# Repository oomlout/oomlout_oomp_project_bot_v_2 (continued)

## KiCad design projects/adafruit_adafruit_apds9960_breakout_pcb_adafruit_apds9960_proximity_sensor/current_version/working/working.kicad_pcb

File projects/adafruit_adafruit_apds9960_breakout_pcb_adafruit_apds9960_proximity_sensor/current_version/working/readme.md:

# adafruit_apds9960_breakout_pcb
 
## summary 
* id: adafruit_adafruit_apds9960_breakout_pcb_adafruit_apds9960_proximity_sensor
* user: adafruit
* name: adafruit_apds9960_breakout_pcb
* board: adafruit_apds9960_proximity_sensor
* repo: https://github.com/adafruit/Adafruit-APDS9960-Breakout-PCB

* src_file_repo_sch: 
* src_file_repo_sch_link: https://github.com/adafruit/Adafruit-APDS9960-Breakout-PCB/tree/master/
* full details link: https://github.com/oomlout/oomlout_oomp_project_bot_v_2/tree/main/projects/adafruit_adafruit_apds9960_breakout_pcb_adafruit_apds9960_proximity_sensor/current_version/working  

## schematic  
  
[schematic (pdf)](working_schematic.pdf) 

## pcb  

[board (pdf)](working.pdf)  

## working_bom
| Id | Designator | Footprint | Quantity | Designation | Supplier and ref |  | None | 
| --- | --- | --- | --- | --- | --- | --- | --- | 
| 1 | U$17,U$21,U$1,U$19 | MOUNTINGHOLE_2.5_PLATED | 4 | MOUNTINGHOLE2.5 |  |  | [''] | 
| 2 | D1 | CHIPLED_0603_NOOUTLINE | 1 | GREEN |  |  | [''] | 
| 3 | Q2 | SOT363 | 1 | BSS138 |  |  | [''] | 
| 4 | CONN3,CONN4 | JST_SH4 | 2 | STEMMA_I2C_QT |  |  | [''] | 
| 5 | R1,R2 | 0603-NO | 2 | 10K |  |  | [''] | 
| 6 | U$22,U$2 | ADAFRUIT_3.5MM | 2 |  |  |  | [''] | 
| 7 | C3,C2 | 0805-NO | 2 | 10uF |  |  | [''] | 
| 8 | FID4,FID3 | FIDUCIAL_1MM | 2 | FIDUCIAL_1MM |  |  | [''] | 
| 9 | C1 | 0603-NO | 1 | 0.1uF |  |  | [''] | 
| 10 | U3 | APDS-9960 | 1 | APDS-9960 |  |  | [''] | 
| 11 | JP1 | 1X06_ROUND_70 | 1 |  |  |  | [''] | 
| 12 | U2 | SOT23-5 | 1 | AP2112K-3.3 |  |  | [''] | 
| 13 | R3 | RESPACK_4X0603 | 1 | 10K |  |  | [''] | 
| 14 | U$31,U$30 | STEMMAQT | 2 |  |  |  | [''] | 
| 15 | U$25 | PCBFEAT-REV-040 | 1 |  |  |  | [''] | 

## bom_schematic
| Ref | Qnty | Value | Cmp name | Footprint | Description | Vendor | DNP | 
| --- | --- | --- | --- | --- | --- | --- | --- | 
| C1 | 1 | 0.1uF | CAP_CERAMIC0603_NO | working:0603-NO |  |  |  | 
| C2, C3 | 2 | 10uF | CAP_CERAMIC0805-NOOUTLINE | working:0805-NO |  |  |  | 
| CONN3, CONN4 | 2 | STEMMA_I2C_QT | STEMMA_I2C_QT | working:JST_SH4 |  |  |  | 
| D1 | 1 | GREEN | LED0603_NOOUTLINE | working:CHIPLED_0603_NOOUTLINE |  |  |  | 
| FID3, FID4 | 2 | FIDUCIAL_1MM | FIDUCIAL_1MM | working:FIDUCIAL_1MM |  |  |  | 
| JP1 | 1 | HEADER-1X670MIL | HEADER-1X670MIL | working:1X06_ROUND_70 |  |  |  | 
| Q2 | 1 | BSS138 | MOSFET-N_DUAL | working:SOT363 |  |  |  | 
| R1, R2 | 2 | 10K | RESISTOR_0603_NOOUT | working:0603-NO |  |  |  | 
| R3 | 1 | 10K | RESISTOR_4PACK | working:RESPACK_4X0603 |  |  |  | 
| U2 | 1 | AP2112K-3.3 | VREG_SOT23-5 | working:SOT23-5 |  |  |  | 
| U3 | 1 | APDS-9960 | APDS-9960 | working:APDS-9960 |  |  |  | 
| U$1, U$17, U$19, U$21 | 4 | MOUNTINGHOLE2.5 | MOUNTINGHOLE2.5 | working:MOUNTINGHOLE_2.5_PLATED |  |  |  | 

## mounting_holes
| x | y | package | value | ref | size | 
| --- | --- | --- | --- | --- | --- | 
| 0.0 | 12.7 | MOUNTINGHOLE_2.5_PLATED | MOUNTINGHOLE2.5 | U$1 | m3 | 
| 20.32 | 12.7 | MOUNTINGHOLE_2.5_PLATED | MOUNTINGHOLE2.5 | U$17 | m3 | 
| 0.0 | 0.0 | MOUNTINGHOLE_2.5_PLATED | MOUNTINGHOLE2.5 | U$19 | m3 | 
| 20.32 | 0.0 | MOUNTINGHOLE_2.5_PLATED | MOUNTINGHOLE2.5 | U$21 | m3 |

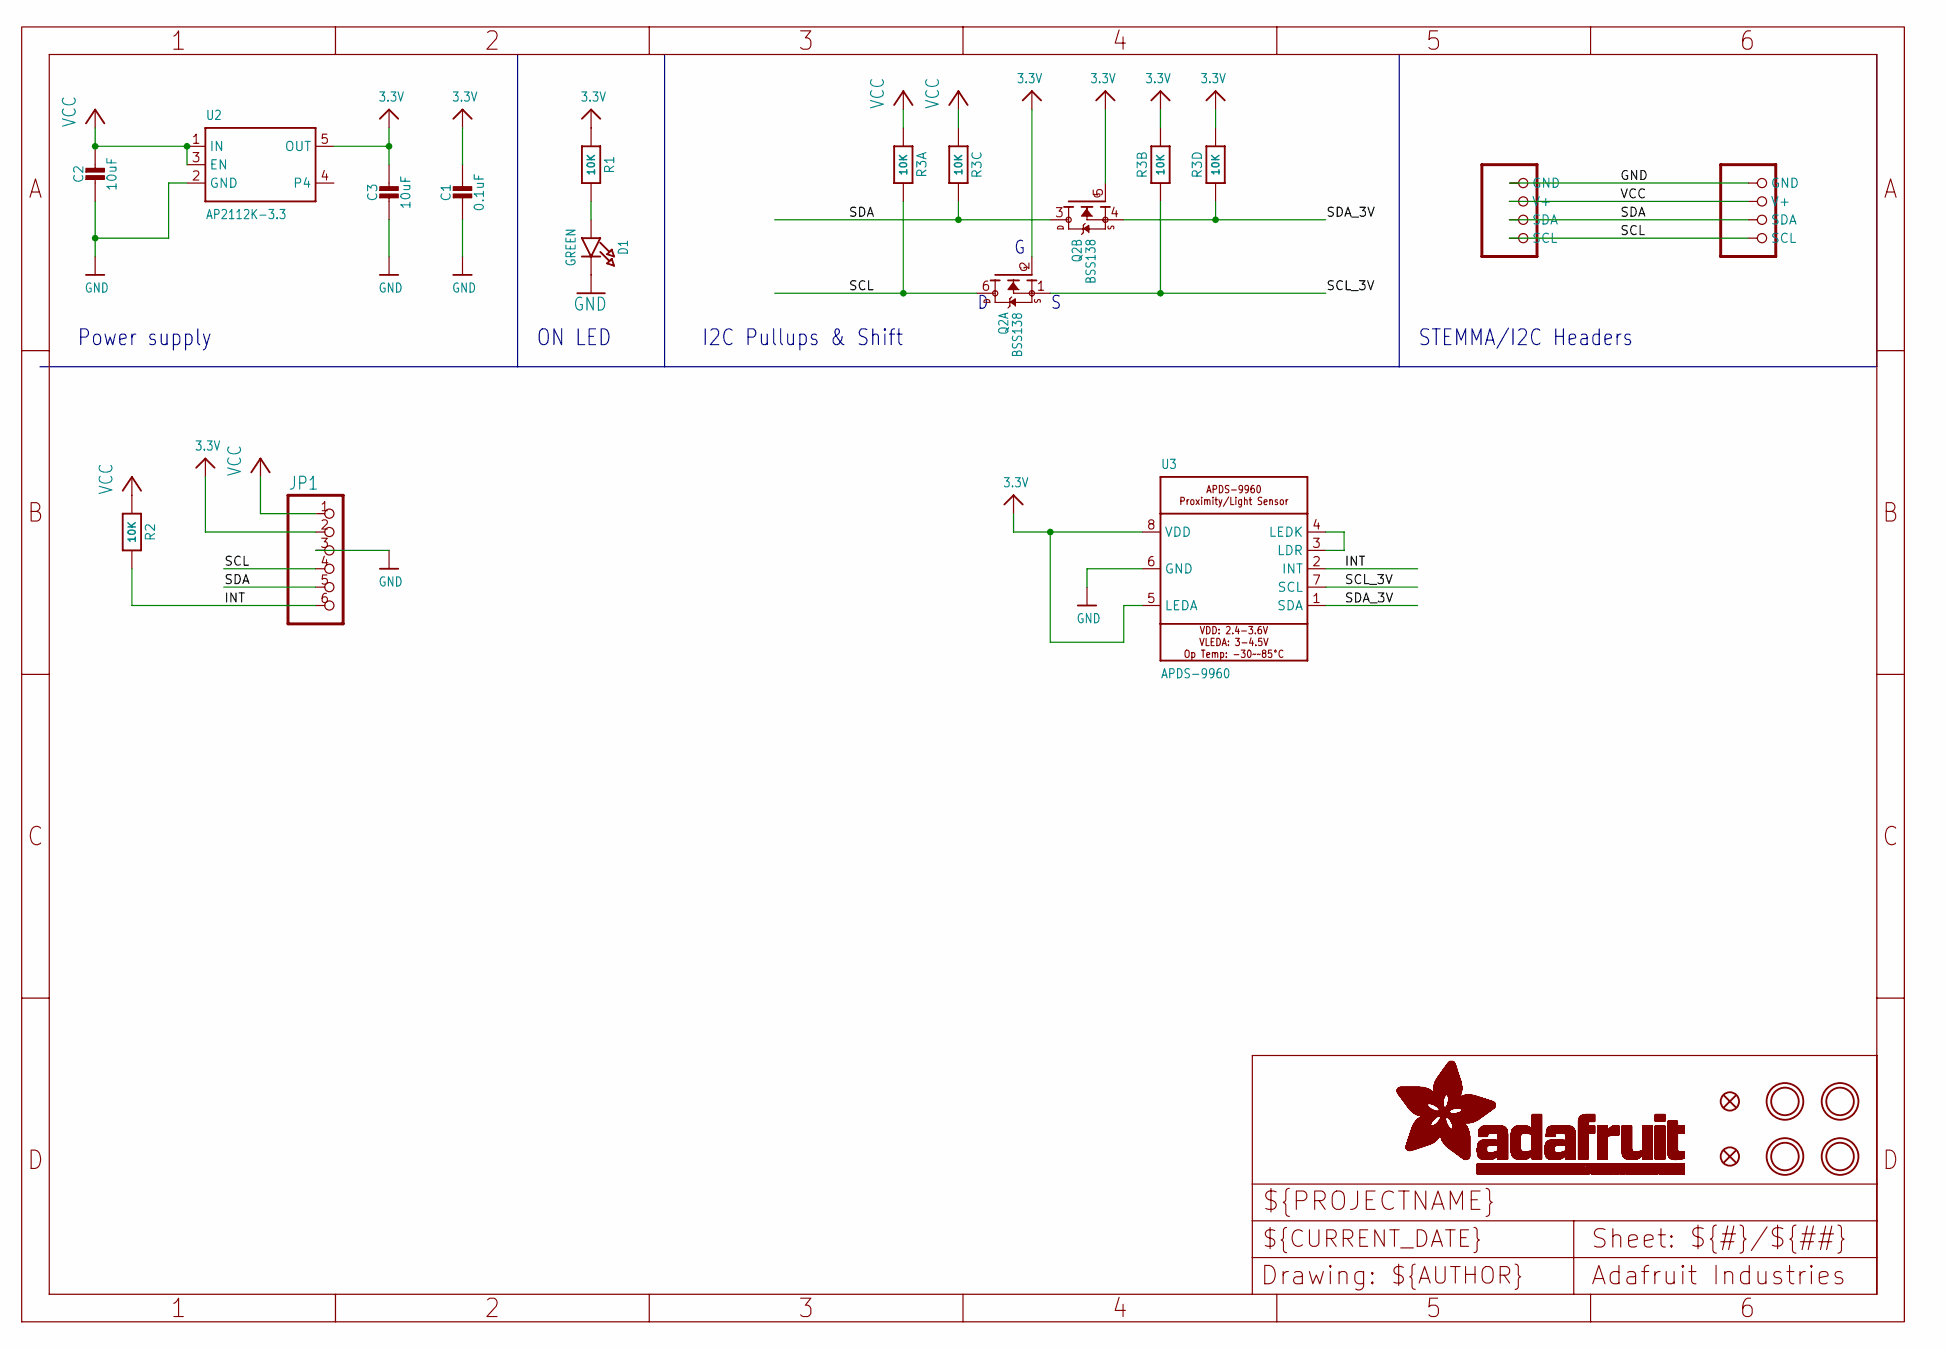
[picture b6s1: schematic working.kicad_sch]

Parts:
C1: 0.1uF; 0603-NO
C2, C3: 10uF; 0805-NO
CONN3, CONN4: STEMMA_I2C_QT; JST_SH4
D1: GREEN; CHIPLED_0603_NOOUTLINE
FID3, FID4: FIDUCIAL_1MM
JP1: HEADER-1X670MIL; 1X06_ROUND_70
Q2: BSS138; SOT363
R1, R2: 10K; 0603-NO
R3: 10K; RESPACK_4X0603
U2: AP2112K-3.3; SOT23-5
U3: APDS-9960
U$1, U$17, U$19, U$21: MOUNTINGHOLE2.5; MOUNTINGHOLE_2.5_PLATED

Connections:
3.3V: C1.1, C3.1, JP1.2, Q2.2 (G), Q2.5 (G), R1.1, R3.2 (1), R3.4 (1), U2.5 (OUT), U3.5 (LEDA), U3.8 (VDD)
GND: C1.2, C2.2, C3.2, CONN3.1 (GND), CONN4.1 (GND), D1.C, JP1.3, U2.2 (GND), U3.6 (GND)
INT: JP1.6, R2.2, U3.2 (INT)
unnamed: D1.A, R1.2
unnamed: U3.3 (LDR), U3.4 (LEDK)
SCL: CONN3.4 (SCL), CONN4.4 (SCL), JP1.4, Q2.6 (D), R3.8 (2)
SCL_3V: Q2.1 (S), R3.7 (2), U3.7 (SCL)
SDA: CONN3.3 (SDA), CONN4.3 (SDA), JP1.5, Q2.3 (D), R3.6 (2)
SDA_3V: Q2.4 (S), R3.5 (2), U3.1 (SDA)
VCC: C2.1, CONN3.2 (V+), CONN4.2 (V+), JP1.1, R2.1, R3.1, R3.3 (1), U2.1 (IN), U2.3 (EN)

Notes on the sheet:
ON LED
Power supply
I2C Pullups & Shift
STEMMA/I2C Headers

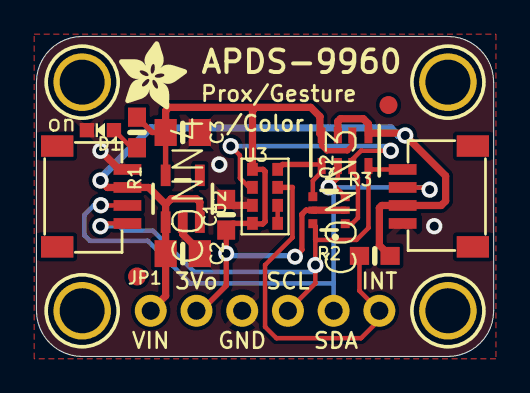
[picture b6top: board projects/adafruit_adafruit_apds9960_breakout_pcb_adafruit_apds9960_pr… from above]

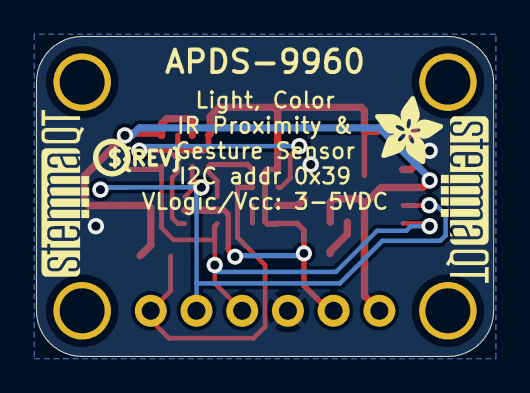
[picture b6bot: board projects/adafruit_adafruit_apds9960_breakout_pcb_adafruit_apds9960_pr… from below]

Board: 2 copper layers, 25.4 x 17.8 mm, 24 parts (4 on the bottom side), 10 nets.

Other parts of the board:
U$2, U$22: ADAFRUIT_3.5MM
U$25: PCBFEAT-REV-040
U$30, U$31: STEMMAQT

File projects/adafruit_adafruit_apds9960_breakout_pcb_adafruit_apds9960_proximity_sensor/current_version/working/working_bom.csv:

"Id";"Designator";"Footprint";"Quantity";"Designation";"Supplier and ref";
1;"U$17,U$21,U$1,U$19";"MOUNTINGHOLE_2.5_PLATED";4;"MOUNTINGHOLE2.5";;;
2;"D1";"CHIPLED_0603_NOOUTLINE";1;"GREEN";;;
3;"Q2";"SOT363";1;"BSS138";;;
4;"CONN3,CONN4";"JST_SH4";2;"STEMMA_I2C_QT";;;
5;"R1,R2";"0603-NO";2;"10K";;;
6;"U$22,U$2";"ADAFRUIT_3.5MM";2;"";;;
7;"C3,C2";"0805-NO";2;"10uF";;;
8;"FID4,FID3";"FIDUCIAL_1MM";2;"FIDUCIAL_1MM";;;
9;"C1";"0603-NO";1;"0.1uF";;;
10;"U3";"APDS-9960";1;"APDS-9960";;;
11;"JP1";"1X06_ROUND_70";1;"";;;
12;"U2";"SOT23-5";1;"AP2112K-3.3";;;
13;"R3";"RESPACK_4X0603";1;"10K";;;
14;"U$31,U$30";"STEMMAQT";2;"";;;
15;"U$25";"PCBFEAT-REV-040";1;"";;;

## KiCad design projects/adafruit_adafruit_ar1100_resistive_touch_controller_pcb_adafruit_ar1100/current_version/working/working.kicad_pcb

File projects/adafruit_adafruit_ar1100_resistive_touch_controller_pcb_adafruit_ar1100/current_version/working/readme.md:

# adafruit_ar1100_resistive_touch_controller_pcb
 
## summary 
* id: adafruit_adafruit_ar1100_resistive_touch_controller_pcb_adafruit_ar1100
* user: adafruit
* name: adafruit_ar1100_resistive_touch_controller_pcb
* board: adafruit_ar1100
* repo: https://github.com/adafruit/Adafruit-AR1100-Resistive-Touch-Controller-PCB

* src_file_repo_sch: 
* src_file_repo_sch_link: https://github.com/adafruit/Adafruit-AR1100-Resistive-Touch-Controller-PCB/tree/master/
* full details link: https://github.com/oomlout/oomlout_oomp_project_bot_v_2/tree/main/projects/adafruit_adafruit_ar1100_resistive_touch_controller_pcb_adafruit_ar1100/current_version/working  

## schematic  
  
[schematic (pdf)](working_schematic.pdf) 

## pcb  

[board (pdf)](working.pdf)  

## working_bom
| Id | Designator | Footprint | Quantity | Designation | Supplier and ref |  | None | 
| --- | --- | --- | --- | --- | --- | --- | --- | 
| 1 | FID1,FID3,FID2 | FIDUCIAL_1MM | 3 | FIDUCIAL" |  |  | [''] | 
| 2 | U$6,U$5,U$4,U$2 | MOUNTINGHOLE_2.5_PLATED | 4 | MOUNTINGHOLE2.5 |  |  | [''] | 
| 3 | D2,D3 | SOD-323F | 2 | 1N4148 |  |  | [''] | 
| 4 | IC1 | TSSOP20-5.3MMBODY | 1 | AR1100_SSOP |  |  | [''] | 
| 5 | C1 | 0805-NO | 1 | 0.1uF |  |  | [''] | 
| 6 | LED1 | CHIPLED_0805_NOOUTLINE | 1 | RED |  |  | [''] | 
| 7 | U$7 | FPC_CONN_1MM_DUAL_4P | 1 | FPC_4PIN_12969 |  |  | [''] | 
| 8 | X1 | USB-MINIB | 1 |  |  |  | [''] | 
| 9 | C2,C3 | 0805-NO | 2 | 10uF |  |  | [''] | 
| 10 | CN2,CN1 | 1X04-CLEANBIG | 2 | 1X4-CLEANBIG |  |  | [''] | 
| 11 | U$14 | ADAFRUIT_3.5MM | 1 |  |  |  | [''] | 
| 12 | R2 | 0805-NO | 1 | 20K |  |  | [''] | 
| 13 | R1 | 0805-NO | 1 | 470 |  |  | [''] | 
| 14 | Y1 | RESONATOR-SMD | 1 | 12MHz |  |  | [''] | 
| 15 | U$17 | ADAFRUIT_TEXT_20MM | 1 |  |  |  | [''] | 

## mounting_holes
| x | y | package | value | ref | size | 
| --- | --- | --- | --- | --- | --- | 
| 0.0 | 0.0 | MOUNTINGHOLE_2.5_PLATED | MOUNTINGHOLE2.5 | U$2 | m3 | 
| 0.0 | 15.24 | MOUNTINGHOLE_2.5_PLATED | MOUNTINGHOLE2.5 | U$4 | m3 | 
| 22.86 | 15.24 | MOUNTINGHOLE_2.5_PLATED | MOUNTINGHOLE2.5 | U$5 | m3 | 
| 22.86 | 0.0 | MOUNTINGHOLE_2.5_PLATED | MOUNTINGHOLE2.5 | U$6 | m3 |

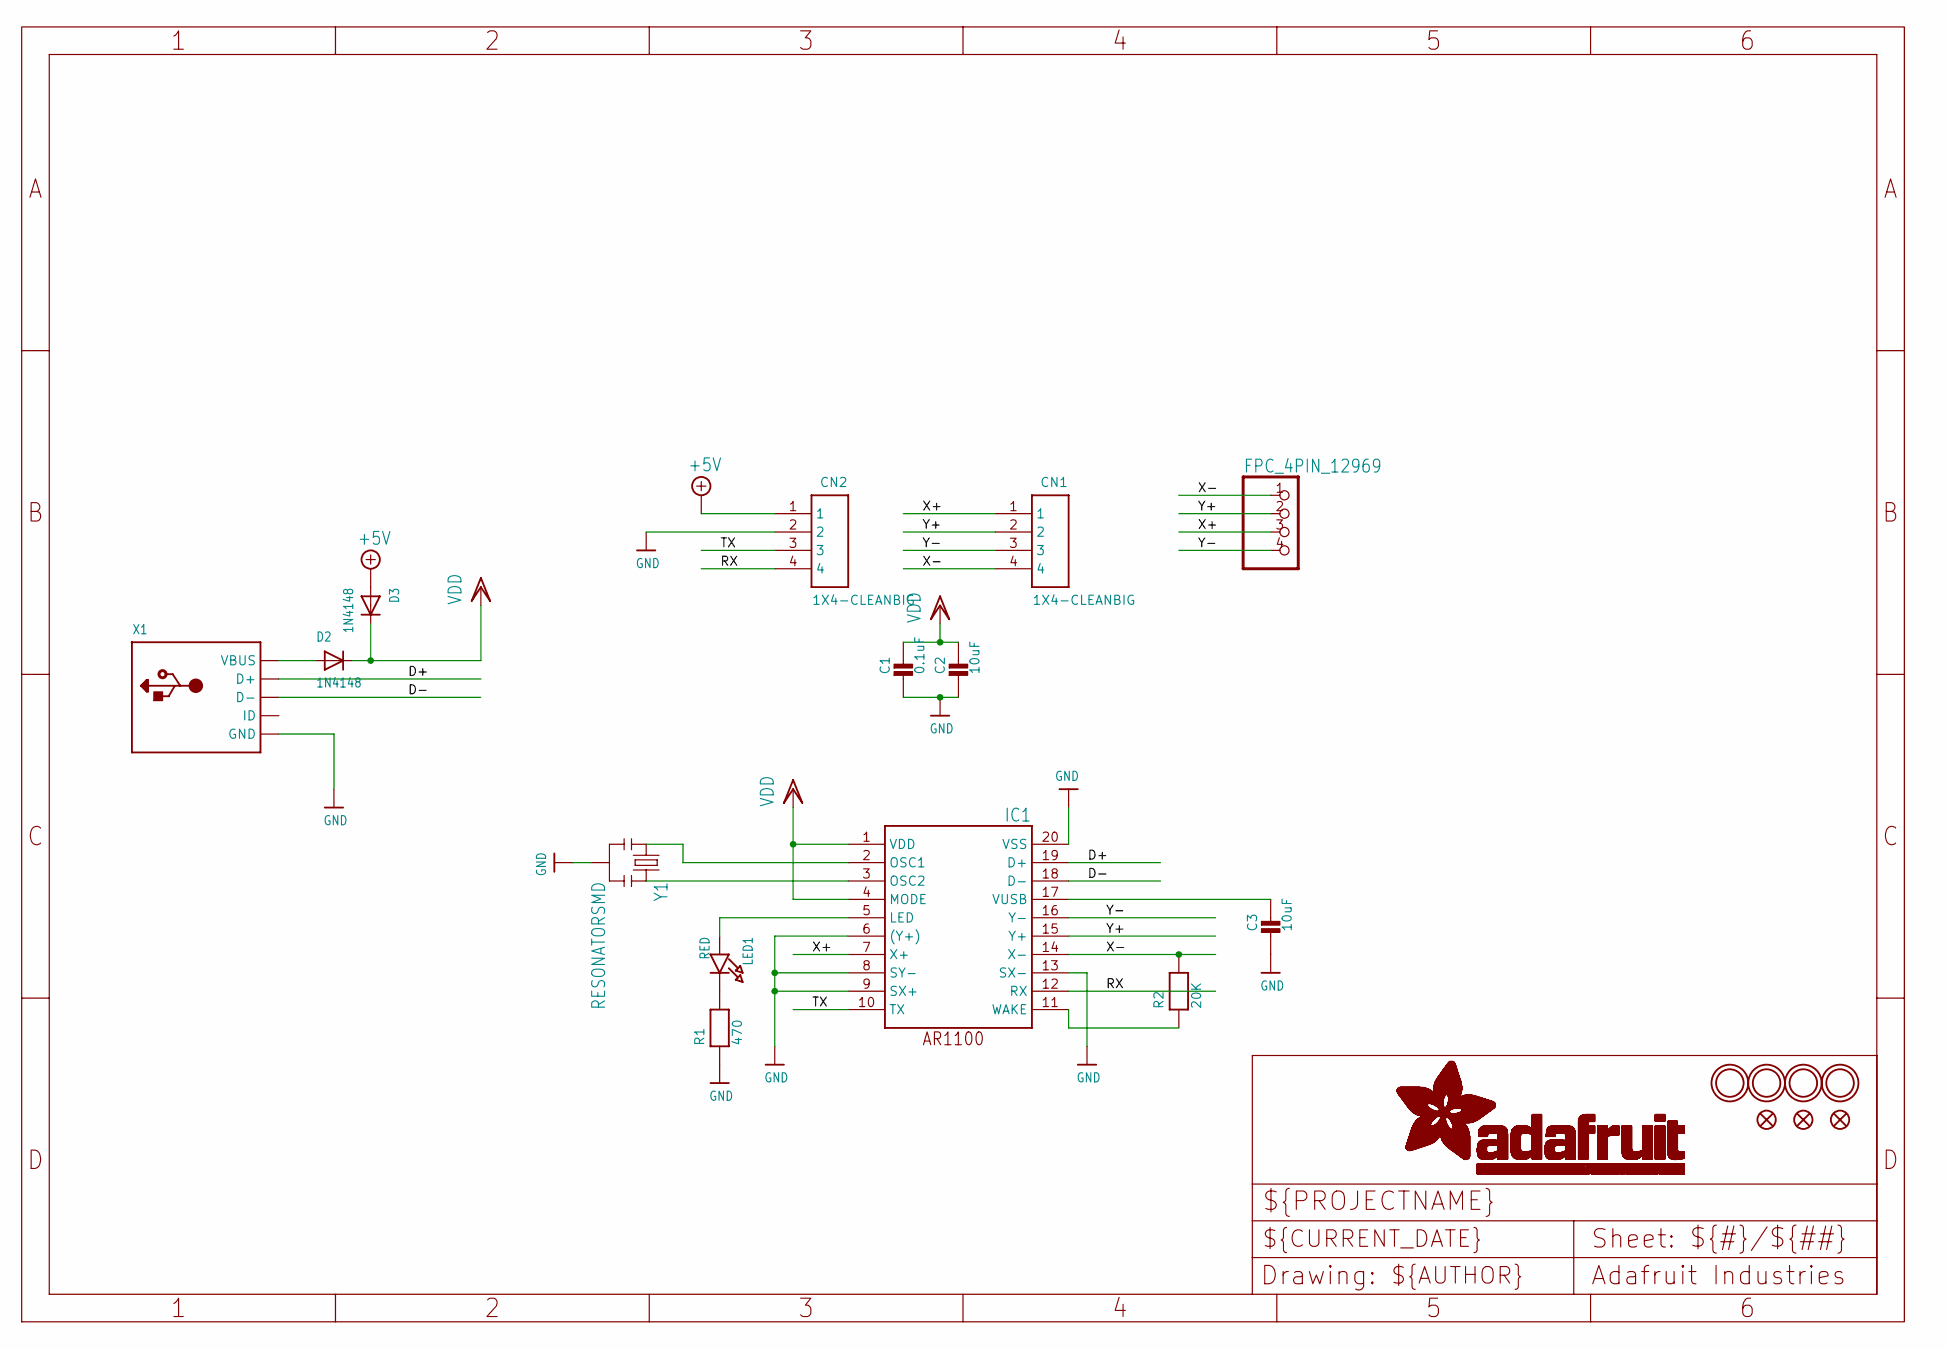
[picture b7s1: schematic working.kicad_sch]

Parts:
C1: 0.1uF; 0805-NO
C2, C3: 10uF; 0805-NO
CN1, CN2: 1X4-CLEANBIG; 1X04-CLEANBIG
D2, D3: 1N4148; SOD-323F
FID1, FID2, FID3: FIDUCIAL""; FIDUCIAL_1MM
IC1: AR1100_SSOP; TSSOP20-5.3MMBODY
LED1: RED; CHIPLED_0805_NOOUTLINE
R1: 470; 0805-NO
R2: 20K; 0805-NO
U$2, U$4, U$5, U$6: MOUNTINGHOLE2.5; MOUNTINGHOLE_2.5_PLATED
U$7: FPC_4PIN_12969; FPC_CONN_1MM_DUAL_4P
X1: USBMINIB; USB-MINIB
Y1: RESONATORSMD; RESONATOR-SMD

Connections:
+5V: CN2.1, D3.A
D+: IC1.19 (D+), X1.D+
D-: IC1.18 (D-), X1.D-
GND: C1.2, C2.2, C3.2, CN2.2, IC1.6 ((Y+)), IC1.8 (SY-), IC1.9 (SX+), IC1.13 (SX-), IC1.20 (VSS), R1.1, X1.GND, X1.GND1 (GND), X1.GND2 (GND), X1.GND3 (GND), X1.GND4 (GND), Y1.2
unnamed: D2.A, X1.VBUS
unnamed: IC1.5 (LED), LED1.A
unnamed: LED1.C, R1.2
unnamed: C3.1, IC1.17 (VUSB)
unnamed: IC1.11 (WAKE), R2.1
unnamed: IC1.3 (OSC2), Y1.3
unnamed: IC1.2 (OSC1), Y1.1
RX: CN2.4, IC1.12 (RX)
TX: CN2.3, IC1.10 (TX)
VDD: C1.1, C2.1, D2.C, D3.C, IC1.1 (VDD), IC1.4 (MODE)
X+: CN1.1, IC1.7 (X+), U$7.3 (2)
X-: CN1.4, IC1.14 (X-), R2.2, U$7.1 (4)
Y+: CN1.2, IC1.15 (Y+), U$7.2 (3)
Y-: CN1.3, IC1.16 (Y-), U$7.4 (1)

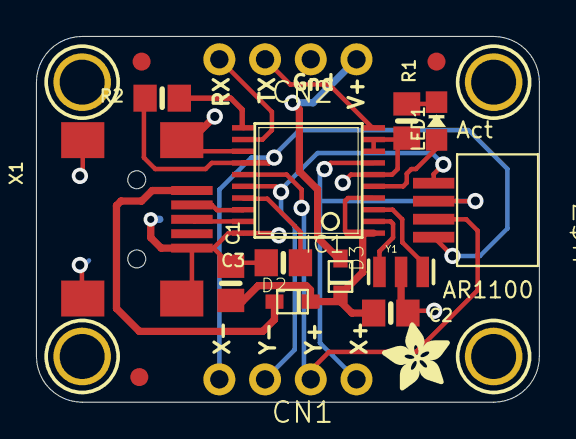
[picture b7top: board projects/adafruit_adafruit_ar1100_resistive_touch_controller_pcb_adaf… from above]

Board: 2 copper layers, 27.9 x 20.3 mm, 23 parts (1 on the bottom side), 18 nets.

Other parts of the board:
U$14: ADAFRUIT_3.5MM
U$17: ADAFRUIT_TEXT_20MM
